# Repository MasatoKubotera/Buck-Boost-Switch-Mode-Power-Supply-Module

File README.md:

<html lang="en">

<head>
	<meta charset="uft-8">
	<meta name="author" content="Masato Kubotera">
    <meta name="description" content="">
</head>

<body>
    <p><strong>This product is currently under development!</strong></p>
	<h1>Buck-Boost Switch Mode Power Supply Module</h1>
        <p>
            <table>
                <tr>
                    <th>Top Surface of PCB</th>
                    <th>Bottom Surface of PCB</th>
                    <th>Assembled Electronic Components</th>
                </tr>
                <tr>
                    <td></td>
                    <td></td>
                    <td></td>
                </tr>
            </table>
        </p>
	<h2>Features Rev. 1</h2>
        <p>
            This product is a buck-boost switch mode power supply module using Analog Devices <a href="https://www.analog.com/en/products/ltm8055.html">LTM8055</a>. Supports the wide voltage input range of 5V to 36V. The output current and switching frequency are determined by the resistor value to be mounted.<br>
            This product was designed with a recommended 12V/6A output and a switching frequency of 600kHz. However, it was later changed to 18V/5A output and 800kHz switching frequency to suit SUSTAINA-OP<sup>TM</sup> applications.
        </p>
    <h3>PCB</h3>
        <p>
            <ul>
                <li>12" x 7" (30.48 mm x 17.78 mm) PCB layout</li>
                <li>1" (2.54mm) pitch through-holes for pin headers
                    <ul>
                        <li>1 x 7 pin headers - 1
                            <ul>
                                <li><strong>3x VIN</strong>: Power In (5V to 36V)</li>
                                <li><strong>1x NC</strong>: Non Connection</li>
                                <li><strong>3x GND</strong>: Common Ground</li>
                            </ul>
                        </li>
                        <li>1 x 7 pin headers - 2
                            <ul>
                                <li><strong>3x VOUT</strong>: Power Out (Regulated 18V)</li>
                                <li><strong>1x NC</strong> Non Connection</li>
                                <li><strong>3x GND</strong>: Common Ground</li>
                            </ul>
                        </li> 
                    </ul>
                </li>
            </ul>
            
        </p>
    <h3><a href="https://www.analog.com/en/products/ltm8055.html">LTM8055</a></h3>
        <p>
            <ul>
                <li>Complete Buck-Boost Switch Mode Power Supply</li>
                <li>VOUT Equal, Greater, Less Than VIN</li>
                <li>Wide Input Voltage Range: 5V to 36V</li>
                <li>12V/3A Output from 6VIN</li>
                <li>12V/6A Output from 12VIN</li>
                <li>12V/8.5A Output from 24VIN</li>
                <li>Up to 97.5% Efficient</li>
                <li>Adjustable Input and Output Average Current Limits</li>
            </ul>
        <p>
	<h2>Development Environments</h2>
    <p>
        This product is designed with the following software.
            <ul>
                <li><a href="https://www.autodesk.com/products/eagle/overview">Autodesk Eagle 9.6.2</a></li>
            </ul>
    </p>
    <h2>Repository Contents</h2>
        <p>
            <dl>
                <dt><a href="/images">\images</a></dt>
                <dd>PCB preview images and capture of design screen</dd>
                <dt><a href="/libraries">\libraries</a></dt>
                <dd>Libraries used in Autodesk Eagle design</dd>
                <dt><a href="/documents">\documents</a> </dt>
                <dd>Documentation for making and using this product</dd>
                <dt><a href="/pcb_order">\pcb_order</a> </dt>
                <dd>Gerber data and documentation for ordering PCB</dd>
                <dt><a href="/schematic.pdf">schematic.pdf</a></dt>
                <dd>Circuit diagram of this product</dd>
                <dt>*.brd</dt>
                <dd>Board wiring design file by Autodesk Eagle</dd>
                <dt>*.sch</dt>
                <dd>Circuit diagram design file by Autodesk Eagle</dd>
                <dt><a href="/.gitignore">.gitignore</a></dt>
                <dd>A file that tells Git not to track a particular file</dd>            <dt><a href="/LICENSE">LICENSE</a></dt>
                <dd>License to use this product</dd>
            </dl>
        </p>
    <h2>Documentation</h2>
        <p>
            The following documents are available for this product.
            <ul>
                <li><a href="/pcb_order/README.md">\pcb_order\README.md</a>: Information for ordering the PCB</li>
                <li><a href="/documents/BOM.md">\document\BOM.md</a>: List of electronic components assembled on the PCB</li>
            </ul>
        </p>
    <h3>Note</h3>
    <h4>Die due to temperature</h4>
        <p>
            The die temperature of the LTM8055/LTM8055-1 must be lower than the maximum rating of 125°C. Therefore, it is recommended that the following heat sinks be affixed to the LTM8055/LTM8055-1.<br>
            Details: <a href="https://www.analog.com/media/en/technical-documentation/data-sheets/LTM8055-8055-1.pdf#page=18">Analog Devices LTM8055/LTM8055-1 Data Sheet Page#18</a>
            <ul>
                <li><a href="https://amzn.asia/d/5Kmnowi">Awxlumv Aluminum Heatsink 14mm x 14mm x 6mm</a></li>
            </ul>
        </p>
    <h4>Output voltage and switching frequency</h4>
        <p>
            The output voltage of LTM8055/LTM8055-1 is determined by R4 and R5 on the board, and the switching frequency by R3. If the voltage is set other than the recommended configuration voltage, the voltage is determined by the following equation.<br>
            Output voltage [V] = 1.2 * (1 + R4 / R5)<br>
            Details: <a href="https://www.analog.com/media/en/technical-documentation/data-sheets/LTM8055-8055-1.pdf#page=10">Analog Devices LTM8055/LTM8055-1 Data Sheet Page#10</a>
        </p>
    <h2>References</h2>
        <p>
            This product was designed with reference to the following products.
            <ul>
                <li><a href="https://www.analog.com/jp/design-center/evaluation-hardware-and-software/evaluation-boards-kits/dc2017a.html">Analog Devices DC2017A: LTM8055 Demo Board</a></li>
            </ul>
        </p>
    <h2>Contact</h2>
        <p>
            If you have any questions, please contact the designer of this product, Masato Kubodera, by <a href="mailto:masato.kubotera@sustaina-op.com">e-mail</a>.<br>
            E-mail: <a href="mailto:masato.kubotera@sustaina-op.com">masato.kubotera@sustaina-op.com</a>
        </p>
    <h2>License Information</h2>
        <p>
            This product is open source. Please review the <a href="/LICENSE">LICENSE</a> for license information.<br>
            <br>
            This product by Masato Kubotera is licensed under a <a href="http://creativecommons.org/licenses/by-nc-sa/4.0/">Creative Commons Attribution-NonCommercial-ShareAlike 4.0 International License</a>.
        </p>
</body>
</html>

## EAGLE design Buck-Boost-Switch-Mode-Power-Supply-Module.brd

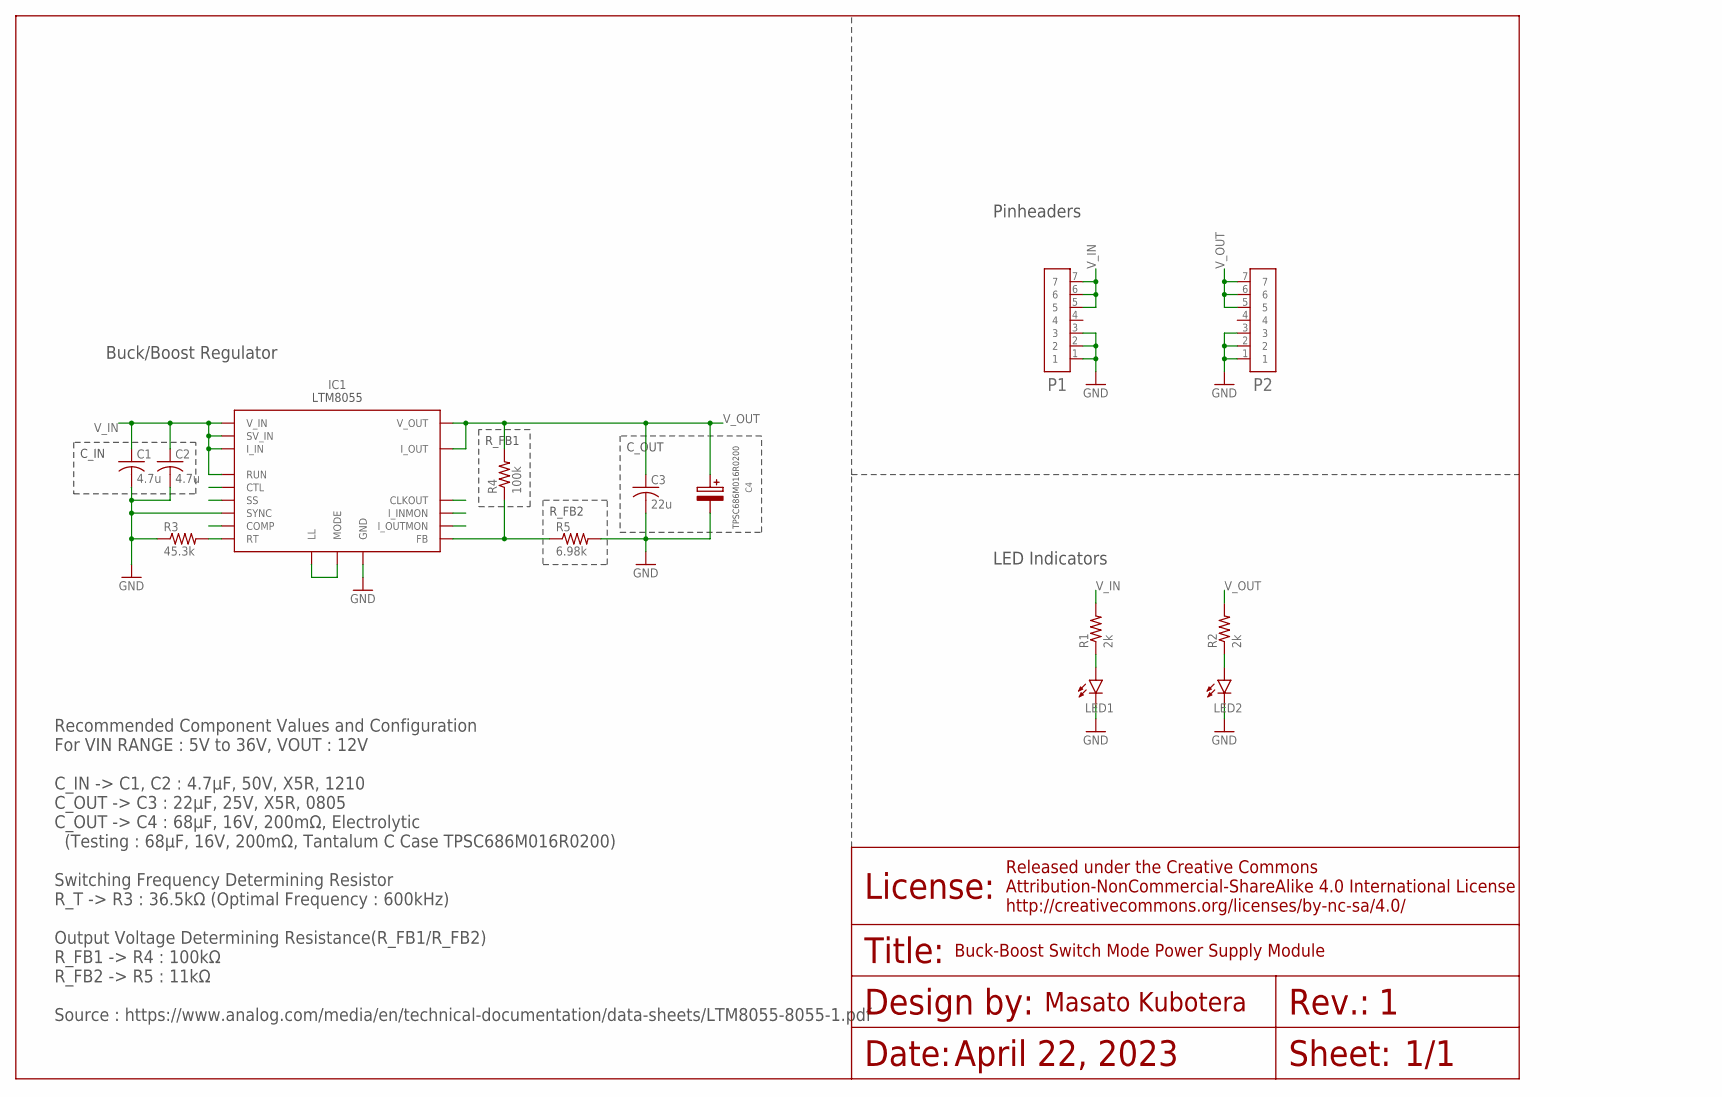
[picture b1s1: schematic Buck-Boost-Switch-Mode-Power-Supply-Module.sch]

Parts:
C1, C2: 4.7u; C0805
C3: 22u; C0805
C4: TPSC686M016R0200
IC1: LTM8055
LED1, LED2: LEDSML0603; SML0603
P1, P2: PINHEADER-7P; 7P
R1, R2: 2k; R0603
R3: 45.3k; R0603
R4: 100k; R0603
R5: 6.98k; R0603

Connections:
CLKOUT: IC1.G1 (CLKOUT)
COMP: IC1.J2 (COMP)
FB: IC1.J1 (FB), R4.1, R5.1
GND: C1.2, C2.2, C3.2, C4.-, IC1.A7 (GND), IC1.A8 (GND), IC1.A9 (GND), IC1.A10 (GND), IC1.A11 (GND), IC1.B7 (GND), IC1.B8 (GND), IC1.B9 (GND), IC1.B10 (GND), IC1.B11 (GND), IC1.C7 (GND), IC1.C8 (GND), IC1.C9 (GND), IC1.C10 (GND), IC1.C11 (GND), IC1.D2 (GND), IC1.D3 (GND), IC1.D4 (GND), IC1.D5 (GND), IC1.D6 (GND), IC1.D7 (GND), IC1.D8 (GND), IC1.D9 (GND), IC1.D10 (GND), IC1.D11 (GND), IC1.E1 (GND), IC1.E2 (GND), IC1.E3 (GND), IC1.E4 (GND), IC1.E5 (GND), IC1.E6 (GND), IC1.E7 (GND), IC1.E8 (GND), IC1.E9 (GND), IC1.E10 (GND), IC1.E11 (GND), IC1.F2 (GND), IC1.F3 (GND), IC1.F4 (GND), IC1.F5 (GND), IC1.F6 (GND), IC1.F7 (GND), IC1.F8 (GND), IC1.F9 (GND), IC1.G3 (GND), IC1.G4 (GND), IC1.G5 (GND), IC1.G6 (GND), IC1.G7 (GND), IC1.G8 (GND), IC1.G9 (GND), IC1.H2 (SYNC), IC1.H3 (GND), IC1.H4 (GND), IC1.H5 (GND), IC1.H6 (GND), IC1.H7 (GND), IC1.H8 (GND), IC1.H9 (GND), IC1.J3 (GND), IC1.J4 (GND), IC1.J5 (GND), IC1.J6 (GND), IC1.J7 (GND), IC1.J8 (GND), IC1.J9 (GND), IC1.K3 (GND), IC1.K4 (GND), IC1.K5 (GND), IC1.K6 (GND), IC1.K7 (GND), IC1.K8 (GND), IC1.K9 (GND), IC1.L1 (GND), IC1.L5 (GND), IC1.L6 (GND), IC1.L7 (GND), IC1.L8 (GND), LED1.C, LED2.C, P1.1, P1.2, P1.3, P2.1, P2.2, P2.3, R3.1, R5.2
I_INMON: IC1.L3 (I_INMON)
I_OUTMON: IC1.L2 (I_OUTMON)
LED1: LED1.A, R1.1
LED2: LED2.A, R2.1
MODE: IC1.F1 (LL), IC1.G2 (MODE)
RT: IC1.H1 (RT), R3.2
SS: IC1.K1 (SS)
STL: IC1.K2 (CTL)
V_IN: C1.1, C2.1, IC1.F10 (SV_IN), IC1.F11 (SV_IN), IC1.G10 (V_IN), IC1.G11 (V_IN), IC1.H10 (V_IN), IC1.H11 (V_IN), IC1.J10 (V_IN), IC1.J11 (V_IN), IC1.K10 (V_IN), IC1.K11 (V_IN), IC1.L4 (RUN), IC1.L9 (I_IN), IC1.L10 (V_IN), IC1.L11 (V_IN), P1.5, P1.6, P1.7, R1.2
V_OUT: C3.1, C4.+, IC1.A1 (V_OUT), IC1.A2 (V_OUT), IC1.A3 (V_OUT), IC1.A4 (V_OUT), IC1.A5 (V_OUT), IC1.A6 (V_OUT), IC1.B1 (V_OUT), IC1.B2 (V_OUT), IC1.B3 (V_OUT), IC1.B4 (V_OUT), IC1.B5 (V_OUT), IC1.B6 (V_OUT), IC1.C1 (V_OUT), IC1.C2 (V_OUT), IC1.C3 (V_OUT), IC1.C4 (V_OUT), IC1.C5 (V_OUT), IC1.C6 (V_OUT), IC1.D1 (I_OUT), P2.5, P2.6, P2.7, R2.2, R4.2

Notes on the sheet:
1/1
April 22, 2023
Buck-Boost Switch Mode Power Supply Module
Buck/Boost Regulator
LED Indicators
Pinheaders
Recommended Component Values and Configuration For VIN RANGE : 5V to 36V, VOUT : 12V C_IN -> C1, C2 : 4.7µF, 50V, X5R, 1210 C_OUT -> C3 : 22µF, 25V, X5R, 0805 C_OUT -> C4 : 68µF, 16V, 200mΩ, Electrolytic (Testing : 68µF, 16V, 200mΩ, Tantalum C Case TPSC686M016R0200) Switching Frequency Determining 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
C_IN
C_OUT
R_FB1
R_FB2

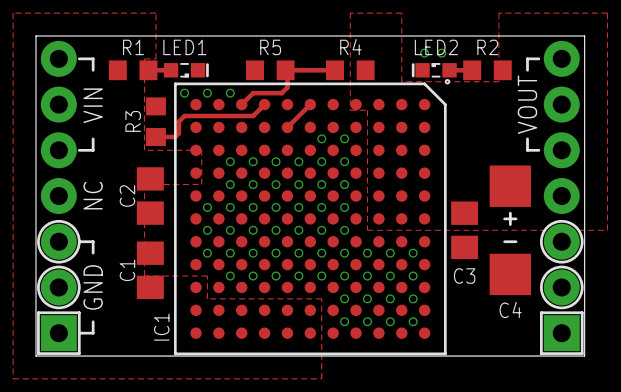
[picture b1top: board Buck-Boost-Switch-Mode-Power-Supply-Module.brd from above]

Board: 2 copper layers, 30.5 x 17.8 mm, 14 parts (0 on the bottom side), 8 nets.

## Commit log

2023-04-23 Initial Upload
2023-04-27 Rename the folder
2023-04-28 Created README.md of PCB ordering
2023-04-29 Create pinout image
2023-09-07 Changed to 18V output configuration used in RoboCup2023

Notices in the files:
parts and their libraries:
Frames: Released under the Creative Commons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
